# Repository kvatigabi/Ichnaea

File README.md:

# Ichnaea
Custom Picoballoon tracker.
- ## Version 1

- ## Version 2

    Much smaller and lighter than Ver.1 with some hardware features moved into software

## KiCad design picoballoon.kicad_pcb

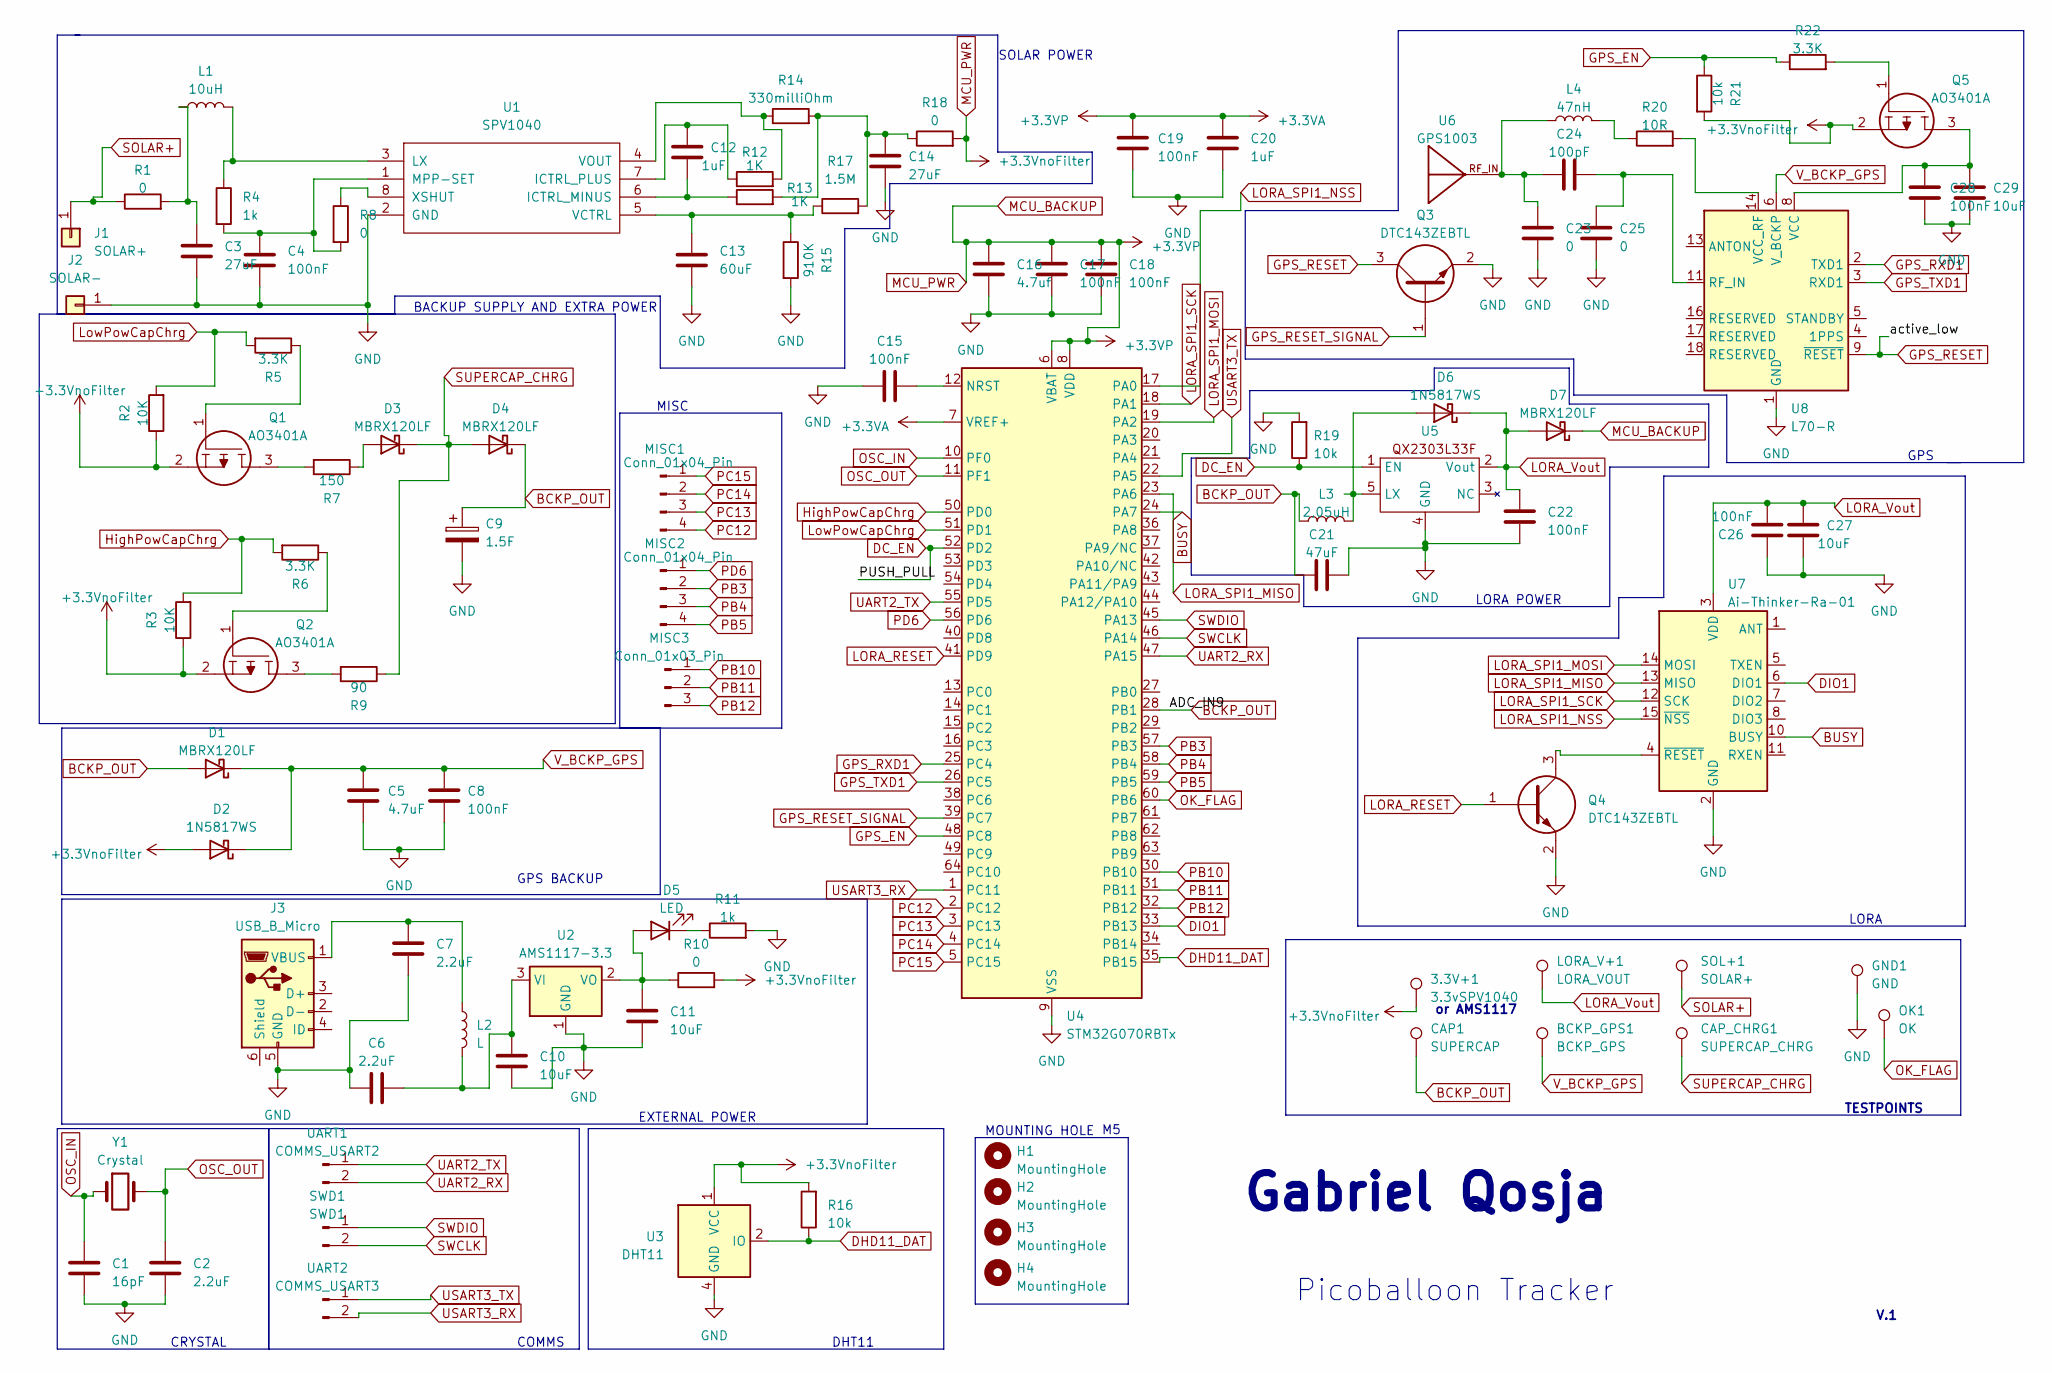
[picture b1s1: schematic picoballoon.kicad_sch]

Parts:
3.3V+1: 3.3vSPV1040; TestPoint_Pad_D3.0mm
BCKP_GPS1: BCKP_GPS; TestPoint_Pad_D3.0mm
C1: 16pF; C_0603_1608Metric
C2, C6, C7: 2.2uF; C_0603_1608Metric
C3, C14: 27uF; C_0603_1608Metric
C4, C8, C15, C17, C18, C19, C22, C26, C28: 100nF; C_0603_1608Metric
C5: 4.7uF; C_0603_1608Metric
C9: 1.5F; CP_Radial_D20mm_P5mm
C10, C11, C27, C29: 10uF; C_0603_1608Metric
C12, C20: 1uF; C_0603_1608Metric
C13: 60uF; C_0603_1608Metric
C16: 4.7uf; C_0603_1608Metric
C21: 47uF; C_0603_1608Metric
C23, C25: 0; C_0603_1608Metric
C24: 100pF; C_0603_1608Metric
CAP1: SUPERCAP; TestPoint_Pad_D3.0mm
CAP_CHRG1: SUPERCAP_CHRG; TestPoint_Pad_D3.0mm
D1, D3, D4, D7: MBRX120LF; D_SOD-123
D2, D6: 1N5817WS; D_SOD-323
D5: LED; LED_D5.0mm
GND1: GND; TestPoint_Pad_D3.0mm
H1, H2, H3, H4: MountingHole; MountingHole_5.3mm_M5
J1: SOLAR+; SolderWire-1.5sqmm_1x01_D1.7mm_OD3.9mm
J2: SOLAR-; SolderWire-1.5sqmm_1x01_D1.7mm_OD3.9mm
J3: USB_B_Micro; USB_Micro-B_Wuerth_629105150521
L1: 10uH; L_0603_1608Metric
L2: L; L_1206_3216Metric_Pad1.42x1.75mm_HandSolder
L3: 2,05uH; L_0603_1608Metric
L4: 47nH; L_0603_1608Metric
LORA_V+1: LORA_VOUT; TestPoint_Pad_D3.0mm
MISC1, MISC2: Conn_01x04_Pin; PinHeader_1x04_P2.54mm_Vertical
MISC3: Conn_01x03_Pin; PinHeader_1x03_P2.54mm_Vertical
OK1: OK; TestPoint_Pad_D3.0mm
Q1, Q2, Q5: AO3401A; SOT-23; Manufacturer_Part_Number AO3401A
Q3, Q4: DTC143ZEBTL; SOT-523; Manufacturer_Part_Number DTC143ZEBTL; Mouser Part Number 755-DTC143ZEBTL
R1, R8, R10, R18: 0; R_0603_1608Metric
R2, R3: 10K; R_Axial_DIN0204_L3.6mm_D1.6mm_P2.54mm_Vertical
R4: 1k; R_0603_1608Metric
R5, R6, R22: 3.3K; R_0603_1608Metric
R7: 150; R_0603_1608Metric
R9: 90; R_0603_1608Metric
R11: 1k; R_Axial_DIN0204_L3.6mm_D1.6mm_P2.54mm_Vertical
R12, R13: 1K; R_0603_1608Metric
R14: 330milliOhm; R_0603_1608Metric
R15: 910K; R_0603_1608Metric
R16: 10k; R_0603_1608Metric
R17: 1.5M; R_0603_1608Metric
R19, R21: 10k; R_Axial_DIN0204_L3.6mm_D1.6mm_P2.54mm_Vertical
R20: 10R; R_0603_1608Metric
SOL+1: SOLAR+; TestPoint_Pad_D3.0mm
SWD1: SWD1; PinHeader_1x02_P1.27mm_Vertical
U1: SPV1040; TSSOP-8_4.4x3mm_P0.65mm
U2: AMS1117-3.3; SOT-223-3_TabPin2
U3: DHT11; Aosong_DHT11_5.5x12.0_P2.54mm
U4: STM32G070RBTx; LQFP-64_10x10mm_P0.5mm
U5: SOT-23-5_HandSoldering
U6: GPS1003
U7: Ai-Thinker-Ra-01; Ai-Thinker-Ra-01-LoRa
U8: L70-R; Quectel_L70-R
UART1: COMMS_USART2; PinHeader_1x02_P1.27mm_Vertical
UART2: COMMS_USART3; PinHeader_1x02_P1.27mm_Vertical
Y1: Crystal; Crystal_HC49-U_Vertical

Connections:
BCKP_OUT: C9.1, C21.2, CAP1.1, D1.2 (A), D4.1 (K), L3.1, U4.28 (PB1)
BUSY: U4.24 (PA7), U7.10 (BUSY)
DC_EN: R19.1, U4.52 (PD2), U5.1 (EN)
DHD11_DAT: R16.1, U3.2 (IO), U4.35 (PB15)
DIO1: U4.33 (PB13), U7.6 (DIO1)
GND: C1.1, C2.1, C3.2, C4.2, C5.2, C6.1, C7.2, C8.2, C9.2, C10.2, C11.2, C13.2, C14.2, C15.1, C16.2, C17.2, C18.2, C19.2, C20.2, C21.1, C22.2, C23.2, C25.2, C26.2, C27.1, C28.2, C29.2, GND1.1, J2.1, J3.5 (GND), Q3.2, Q4.2, R11.2, R15.2, R19.2, U1.2 (GND), U2.1 (GND), U3.4 (GND), U4.9 (VSS), U5.4 (GND), U7.2 (GND), U7.9 (GND), U7.16 (GND), U8.1 (GND), U8.10 (GND), U8.12 (GND)
GPS_EN: R21.1, R22.1, U4.48 (PC8)
GPS_RESET: Q3.3, U8.9 (~RESET)
GPS_RESET_SIGNAL: Q3.1, U4.39 (PC7)
GPS_RXD1: U4.25 (PC4), U8.2 (TXD1)
GPS_TXD1: U4.26 (PC5), U8.3 (RXD1)
HighPowCapChrg: R3.2, R6.2, U4.50 (PD0)
LORA_RESET: Q4.1, U4.41 (PD9)
LORA_SPI1_MISO: U4.23 (PA6), U7.13 (MISO)
LORA_SPI1_MOSI: U4.19 (PA2), U7.14 (MOSI)
LORA_SPI1_NSS: U4.17 (PA0), U7.15 (~NSS)
LORA_SPI1_SCK: U4.18 (PA1), U7.12 (SCK)
LORA_Vout: C22.1, C26.1, C27.2, D6.1 (K), D7.2 (A), LORA_V+1.1, U5.2 (Vout), U7.3 (VDD)
LowPowCapChrg: R2.2, R5.2, U4.51 (PD1)
MCU_BACKUP: 3.3V+1.1, C16.1, C17.1, C18.1, C19.1, C20.1, D2.2 (A), D7.1 (K), Q1.2, Q2.2, Q5.2, R2.1, R3.1, R10.2, R16.2, R18.2, R21.2, U3.1 (VCC), U4.6 (VBAT), U4.7 (VREF+), U4.8 (VDD)
unnamed: C3.1, L1.1, R1.2
unnamed: C14.1, R13.2, R14.2, R17.2, R18.1
unnamed: C23.1, C24.1, L4.1, U6.RF_IN
unnamed: D3.2 (A), R7.1
unnamed: C11.1, D5.2 (A), R10.1, U2.2 (VO)
unnamed: D5.1 (K), R11.1
unnamed: D6.2 (A), L3.2, U5.5 (LX)
unnamed: C7.1, J3.1 (VBUS), L2.1
unnamed: L4.2, R20.1
unnamed: Q1.1, R5.1
unnamed: Q1.3, R7.2
unnamed: Q2.1, R6.1
unnamed: Q2.3, R9.2
unnamed: Q5.1, R22.2
unnamed: C12.1, R13.1, U1.6 (ICTRL_MINUS)
unnamed: C12.2, R12.1, U1.7 (ICTRL_PLUS)
unnamed: L1.2, R4.1, U1.3 (LX)
unnamed: C4.1, R4.2, R8.2, U1.1 (MPP-SET)
unnamed: C13.1, R15.1, R17.1, U1.5 (VCTRL)
unnamed: R12.2, R14.1, U1.4 (VOUT)
unnamed: R8.1, U1.8 (XSHUT)
unnamed: C6.2, C10.1, L2.2, U2.3 (VI)
unnamed: C15.2, U4.12 (NRST)
unnamed: Q4.3, U7.4 (~RESET)
unnamed: C24.2, C25.1, U8.11 (RF_IN)
unnamed: C28.1, C29.1, Q5.3, U8.8 (VCC)
unnamed: R20.2, U8.14 (VCC_RF)
OK_FLAG: OK1.1, U4.60 (PB6)
OSC_IN: C1.2, U4.10 (PF0), Y1.1
OSC_OUT: C2.2, U4.11 (PF1), Y1.2
PB3: MISC2.2, U4.57 (PB3)
PB4: MISC2.3, U4.58 (PB4)
PB5: MISC2.4, U4.59 (PB5)
PB10: MISC3.1, U4.30 (PB10)
PB11: MISC3.2, U4.31 (PB11)
PB12: MISC3.3, U4.32 (PB12)
PC12: MISC1.4, U4.2 (PC12)
PC13: MISC1.3, U4.3 (PC13)
PC14: MISC1.2, U4.4 (PC14)
PC15: MISC1.1, U4.5 (PC15)
PD6: MISC2.1, U4.56 (PD6)
SOLAR+: J1.1, R1.1, SOL+1.1
SUPERCAP_CHRG: CAP_CHRG1.1, D3.1 (K), D4.2 (A), R9.1
SWCLK: SWD1.2, U4.46 (PA14)
SWDIO: SWD1.1, U4.45 (PA13)
UART2_RX: U4.47 (PA15), UART1.2
UART2_TX: U4.55 (PD5), UART1.1
USART3_RX: U4.1 (PC11), UART2.2
USART3_TX: U4.22 (PA5), UART2.1
V_BCKP_GPS: BCKP_GPS1.1, C5.1, C8.1, D1.1 (K), D2.1 (K), U8.6 (V_BCKP)

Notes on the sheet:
or AMS1117
MOUNTING HOLE
Picoballoon Tracker
LORA
SOLAR POWER
LORA POWER
GPS
MISC
Gabriel Qosja
TESTPOINTS
BACKUP SUPPLY AND EXTRA POWER
COMMS
DHT11
EXTERNAL POWER
V.1
GPS BACKUP
CRYSTAL

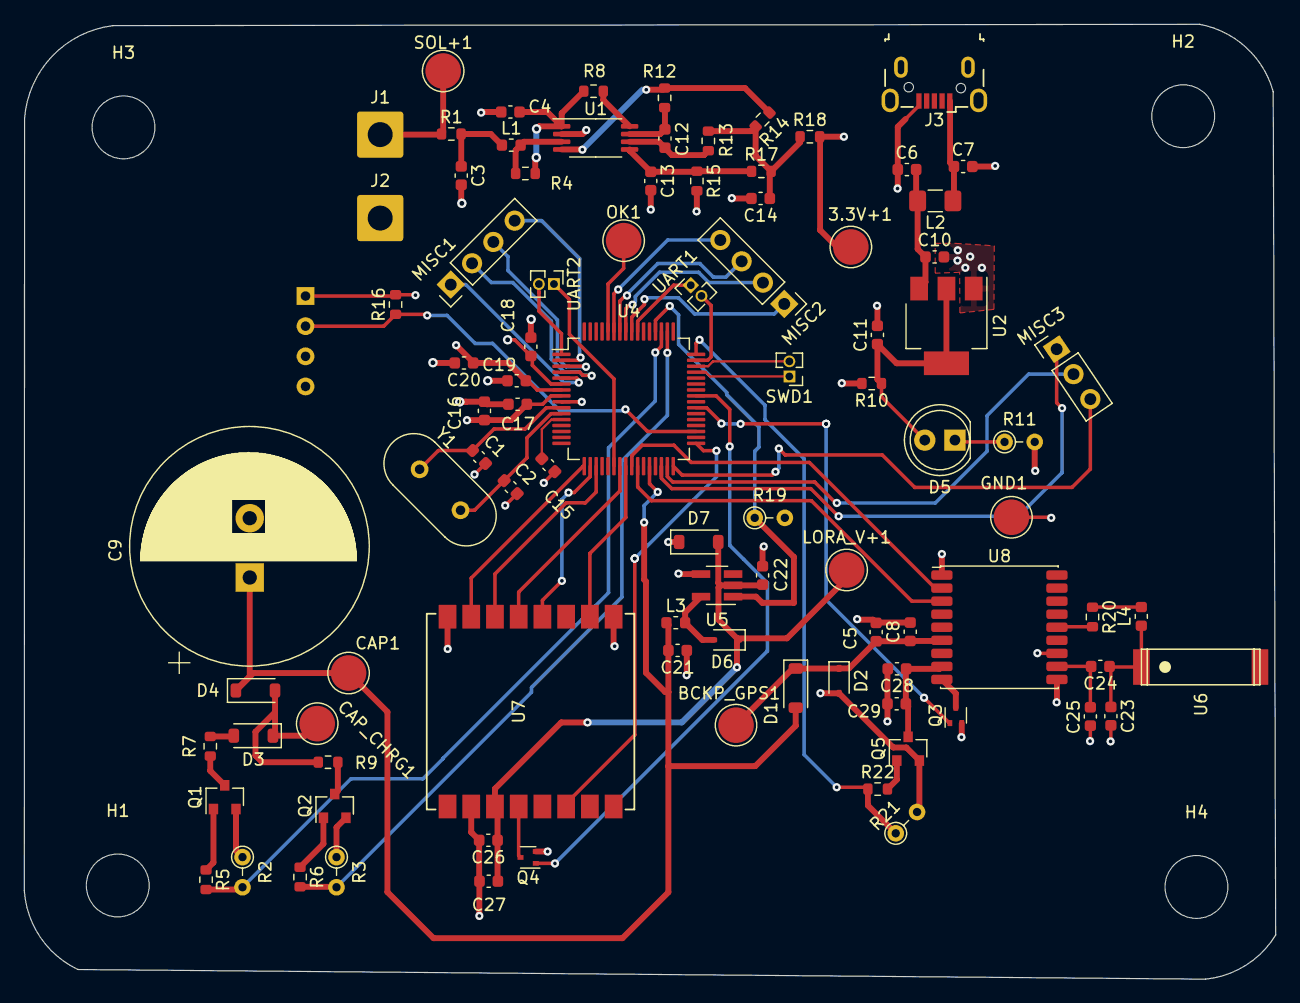
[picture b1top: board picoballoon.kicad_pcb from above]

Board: 4 copper layers, 105.5 x 80.5 mm, 97 parts (1 on the bottom side), 70 nets.

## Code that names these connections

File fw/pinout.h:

#ifndef pinout_h
#define pinout_h




//POWER PINS
#define HighPowCapChrg PD0 //High power cap charging circuit (low value resistor)
#define LowPowCapChrg PD1 //Low power cap charging circuit (high value resistor)
#define CAP_CHRG_V PB1 // ADC_IN9 Cap voltage
#define CAP_CHRG_READ_EN // Enable Cap voltage readout

#define DC_EN PD2 //PUSH_PULL enable lora power
#define LORA_RESET PD9 // LORA reset pin
#define GPS_RESET_SIGNAL PC7
#define GPS_EN PC8 // GPS enable



//LORA
#define LORA_SPI1_NSS PA0 //LORA chipselect
#define LORA_SPI1_MOSI PA2
#define LORA_SPI1_MISO PA6
#define DIO1 PB13 //LORA DIO1
#define DIO2 PA3 //LORA DIO2
#define DIO0 PA7 //LORA DIO0


//COMMS
#define UART2_TX PD5
#define UART2_RX PA15
#define USART3_RX PC11
#define USART3_TX PA5

#ifdef ICHNAE_V1 //V1 board had wrong TX/RX GPS wiring..
#define GPS_RX_USART1 PC5 // GPS Receive (WIRED WRONG FOR VER.1)
#define GPS_TX_USART1 PC4 // GPS transmit (WIRED WRONG FOR VER.1)
//#ifdef ICHNAE_V2
#else
#define GPS_RX_USART1 PC4 // GPS Receive
#define GPS_TX_USART1 PC5 // GPS transmit
#endif

#define SWDIO PA13
#define SWCLK PA14



//MISC
#define MISC2_pin1 PD6
#define MISC2_pin2 PB3
#define MISC2_pin3 PB4
#define MISC2_pin4 PB5


#define MISC1_pin4 PC12
#define MISC1_pin3 PC13
#define MISC1_pin2 PC14
#define MISC1_pin1 PC15

#define MISC3_pin2 PB11

#define DHT11_DAT PB15 //DHT 11 data pin

//PROBEPOINTS
#define OK_FLAG PB6


#endif

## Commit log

2023-07-27 Completed SPV1040 compoment wiring with new solar panel values.
    Also calculated power draw from GPS and MCU in a spreadsheet. These will
    be needed to calculate max power to charge supercap with.
2023-07-28 Completed superCap charging circuit and DC-DC for Lora.
2023-07-30 Fixed supercap charging calculations to display voltage that remains after transmitting LORA payload
2023-07-31 Finalized schematic and added all critical compoments. Minor tweaks will be added along the way.
2023-08-01 Completed PCB routing
2023-08-02 PCB completed and is in production
2023-09-01 Ready for first upload
2023-09-01 Add README
2023-10-20 Create LICENSE
2023-10-20 Added schematic. Also added charging figures.
2023-10-21 Cleanup
2024-06-13 Added pinout and fixed wiring GPS TX/RX was wrongly connected. Added conditional compiling for that and fixed schematic only.
2024-09-06 Added Version 2 of the PCB with inital firmware commit
2024-09-06 Cleanup code
2024-09-08 Created "Point in polygon" algorithm for Geofencing Will be later used to check if we are above a place which we cannot transmit.
2024-09-22 Add supercap charging control and internal ADC channels
2025-02-18 Write STARTUP state (kinda). Coded some stuff better (hopefully).
